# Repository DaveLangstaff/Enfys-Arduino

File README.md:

# Enfys-Arduino

Arduino code for SCPI instrument to control detector board

Dave Langstaff dpl@aber.ac.uk

Code runs on Arduino nano esp 32
Detectorboard EGSE commands
===========================
Deafult baud rate: 57600
All commands temrinated with cr-lf

Identify Command
================
*IDN?    - return identifier string. Eg "Aberystwyth University,Enfys Detector,#01,#05"

Debug Command
=============
*DBG?	 - returns debugging information on current monitors installed

Analog Input
============
AIn#?    - return data from analog inputs (ADC convertor) # is channel 0-7, channel values outside the range 0-7 will return ERR_BAD_SUFFIX -4
		 - This is a summation of OS individual readings and is returned as an unsigned long int

Set Offset DAC		 
==============
DOut# param	 - sets DAC on channel # (where channel 0=SWIR, 1=MWIR, any other # returns ERR_BAD_SUFFIX -4)
             - param is in range 0-4095, values outside this range return ERR_BAD_PARAM -5

Oversampling
============
OS param	 - set oversampling to param, where param is in the range 1-4096 values outside this range return ERR_BAD_PARAM -5
OS?			 - returns current value of oversampling

Clock speed
===========
CLK param    - sets SPI clock speed. Param should be in the range of 1,000,000 to 16,000,000 values outside this range return ERR_BAD_PARAM -5
CLK?         - return current SPI clock speed

Current and Voltage monitoring
==============================
CURR#?			return current from supply #.

					# is in the range 0-3 values outside the range 0-3 will return ERR_BAD_SUFFIX -4
					0: 3.3V supply
					
					1: Heater supply
					
					2: +12V supply
					
					3: -12V supply

VBUS#?			return bus voltage (in mV) from supply #

					# is in the range 0-3 values outside the range 0-3 will return ERR_BAD_SUFFIX -4

					0: 3.3V supply

					1: Heater supply

					2: +12V supply

					3: -12V supply
					
NAME#?			return device name from supply #

					# is in the range 0-3 values outside the range 0-3 will return ERR_BAD_SUFFIX -4

					0: 3.3V supply INA3221

					1: Heater supply INA3221

					2: +12V supply INA3221

					3: -12V supply INA260

TIME?		- gives time in usec for last read operation

BURST#?		- reads OS readings into buffer and returns whole databuffer

SCIENCE? -  reads all 8 ADC channels according to current OS and THROW parameters. Sums readings and then shifts to discard lower 4 bits
         - returns all 8 readings in a comma seperated line

DELAY xxxx 	- sets delay between SPI reads in usec

DELAY?		- returns delay between SPI reads in usec

THROW xxxx	- sets number of readings to throw away at start of each read cycle (0..1024)

THROW?		- returns number of readings to throw away at start of each read cycle (0..1024)					

HTR:ON		- enable on board heater supply

HTR:OFF		- disable on-board heater supply

POwer:ON	- Enable power to detector board

POwer:OFF	- Disable power to detector board

RTD:TEMP?	- get temperature from RTD device

  all commands will return either the requested data (? commands) 
  or an error code indicating successful or otherwise completion

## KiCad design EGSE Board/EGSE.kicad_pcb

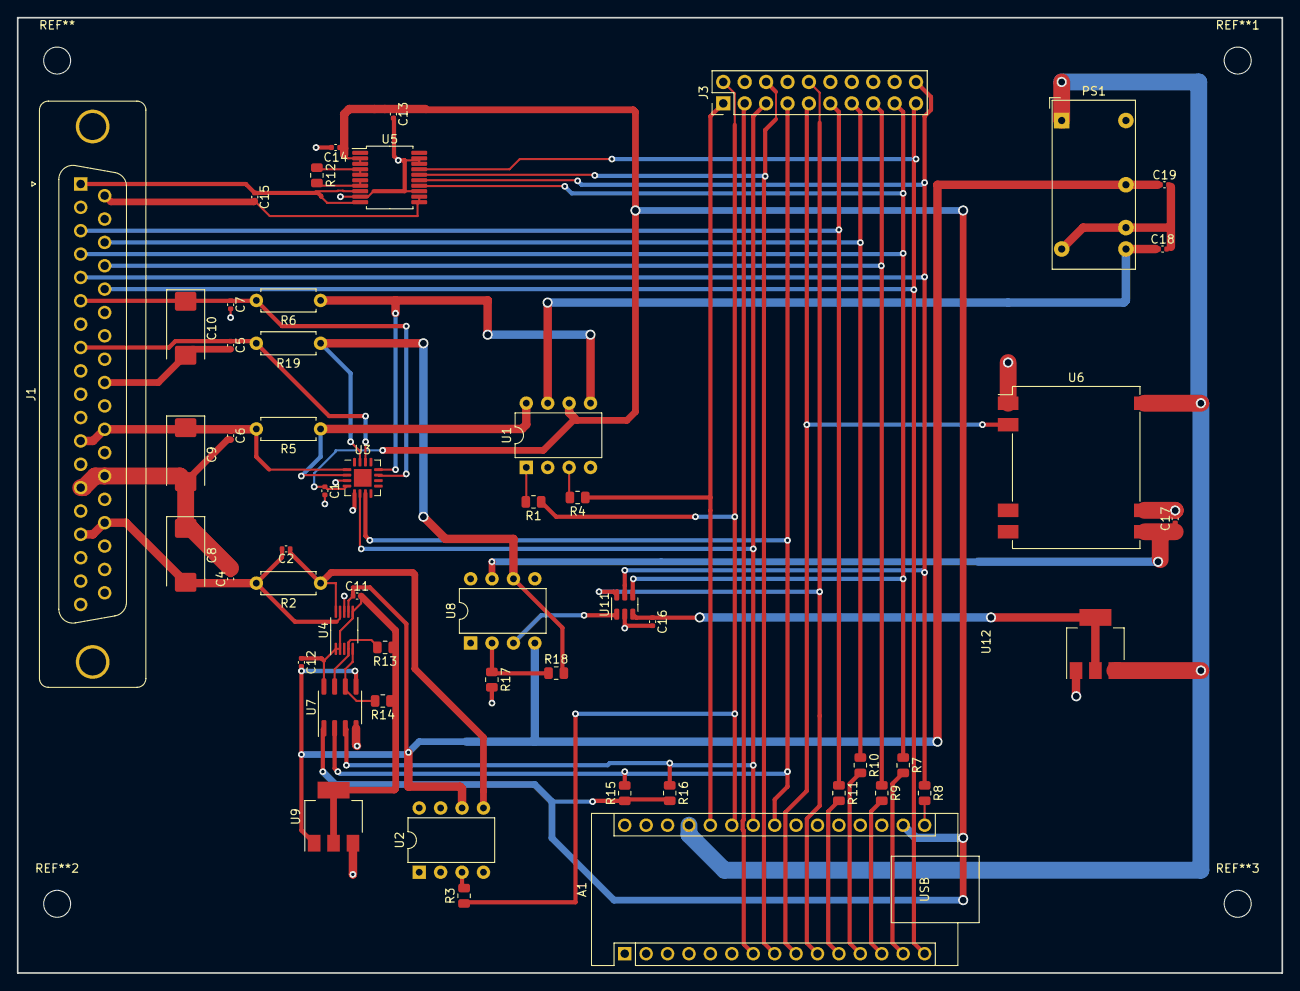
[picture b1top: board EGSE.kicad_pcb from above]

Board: 2 copper layers, 150.0 x 113.3 mm, 52 parts (0 on the bottom side), 46 nets.

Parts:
A1: Arduino_Nano_v2.x; Arduino_Nano
C1, C4, C5, C6, C7, C11, C12, C18, C19: 100nF; C_0402_1005Metric
C2: 10nF; C_0402_1005Metric
C8, C9, C10: 10uF; CP_EIA-7343-31_Kemet-D_Pad2.25x2.55mm_HandSolder
C13, C14, C15, C16, C17: 0.1u; C_0402_1005Metric
J1: DC37_Receptacle; DSUB-37_Female_Vertical_P2.77x2.84mm_MountingHoles
J3: Conn_02x10_Odd_Even; PinHeader_2x10_P2.54mm_Vertical
PS1: IR0512S; Converter_DCDC_XP_POWER-IAxxxxD_THT
R1, R3, R4: 1K; R_0805_2012Metric
R2, R5, R19: 0.1R; R_Axial_DIN0207_L6.3mm_D2.5mm_P7.62mm_Horizontal
R6: 1R; R_Axial_DIN0207_L6.3mm_D2.5mm_P7.62mm_Horizontal
R7, R8, R9, R10, R11: 33R; R_0805_2012Metric
R12: 4K; R_0805_2012Metric
R13, R14, R15, R16, R18: 3k3; R_0805_2012Metric
R17: 1k; R_0805_2012Metric
U1, U2: VOR2121A8; DIP-8_W7.62mm
U3: INA3221; Texas_RGV_S-PVQFN-N16_EP2.1x2.1mm
U4: INA238AQDGSRQ1; VSSOP-10_3x3mm_P0.5mm
U5: MAX31865xAP; SSOP-20_5.3x7.2mm_P0.65mm
U6: ISU0205S15; Converter_DCDC_XP_POWER-ISU02_SMD
U7: ISO1540; SOIC-8_3.9x4.9mm_P1.27mm
U8: OPA551P; DIP-8_W7.62mm
U9, U12: LD1117S33TR_SOT223; SOT-223-3_TabPin2
U11: DAC121S101; SOT-23-6

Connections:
+3.3V: A1.17 (3V3), C1.1, C13.1, C14.1, R15.1, R16.2, U1.6 (S2), U3.4 (VS), U5.2 (DVDD), U5.3 (VDD), U7.1 (VCC1)
+5V: A1.27 (+5V), PS1.1 (+Vin), U6.14 (+VIN), U12.3 (VI)
/-12V_UNSWITCHED: C11.1, C12.2, C19.1, PS1.4 (-Vout), U2.6 (S2), U4.7 (GND), U7.5 (GND2), U8.4 (V-), U9.1 (GND)
/BoardHeater/+12V_HTR: R18.2, R19.1, U3.15 (IN+2), U8.6
/BoardHeater/+15V: C17.1, U6.8 (+VOUT), U8.7 (V+)
/DETEC_+3v3: C7.1, C10.1, J1.6, R6.2, U3.11 (IN-1)
/DETEC_+12VA: C6.1, C9.1, J1.12, J1.30, R5.2, U3.1 (IN-3)
/DETEC_-12VA: C2.2, C4.1, C8.2, J1.16, J1.34, R2.2, U4.9 (IN-)
/DETEC_ADC_CS: J1.23, J3.15, R9.1
/DETEC_HTR: C5.1, J1.8, R19.2, U3.14 (IN-2)
/DETEC_MISO: A1.15 (D12), J1.24, J3.19, U5.17 (SDO)
/DETEC_MOSI: J1.4, J3.17, R7.1, U5.14 (SDI), U11.4 (D_IN)
/DETEC_SCK: J1.5, J3.20, R8.1, U5.15 (SCLK), U11.5 (SCLK)
/DETEC_TRP: C15.1, J1.1, U5.8 (FORCE+), U5.10 (RTDIN+)
/DETEC_TRP_RTN: C15.2, J1.20, U5.11 (RTDIN-), U5.12 (FORCE-)
/EN_3V3: A1.26 (A7), J3.1, R4.1
/EN_12V: A1.25 (A6), J3.2, R1.1, R3.1
/HTR_DAC_CS: A1.10 (D7), J3.10, U11.6 (~SYNC)
/HTR_EN: A1.9 (D6), J3.9, U6.2 (ON/~OFF)
/MWIR_DAC_CS: J1.22, J3.13, R10.1
/PowerSupplies/+12V_Unswitched: C18.1, PS1.6 (+Vout), U1.7 (S1')
/PowerSupplies/SCL2: R14.2, U4.5 (SCL), U7.6 (SCL2)
/PowerSupplies/SDA2: R13.2, U4.4 (SDA), U7.7 (SDA2)
/RTD_MON_CS: A1.8 (D5), J3.6, U5.16 (~CS)
/SCL: A1.24 (A5), J3.5, R16.1, U3.6 (SCL), U7.3 (SCL1)
/SDA: A1.23 (A4), J3.7, R15.2, U3.7 (SDA), U7.2 (SDA1)
/SWIR_DAC_CS: J1.3, J3.11, R11.1
/TRIG: A1.7 (D4), J3.3
GND: A1.4 (GND), A1.29 (GND), C1.2, C4.2, C5.2, C6.2, C7.2, C8.1, C9.2, C10.2, C13.2, C14.2, C16.2, C17.2, C18.2, C19.2, J1.14, J1.25, J1.28, J1.32, J3.4, J3.8, J3.14, J3.18, PS1.2 (-Vin), PS1.5 (0V), R17.2, U1.2, U1.4, U2.4, U3.3 (GND), U3.5 (A0), U4.8 (VBUS), U5.9 (FORCE2), U5.13 (GND), U5.18 (DGND), U5.19 (GND), U6.1 (-VIN), U6.9 (-VOUT), U7.4 (GND1), U9.3 (VI), U11.2 (GND), U12.1 (GND)
unnamed: A1.11 (D8), R11.2
unnamed: A1.12 (D9), R10.2
unnamed: A1.13 (D10), R9.2
unnamed: A1.14 (D11), R7.2
unnamed: A1.16 (D13), R8.2
unnamed: R1.2, U1.1
unnamed: R3.2, U2.3
unnamed: R4.2, U1.3
unnamed: R5.1, U1.8 (S1), U3.2 (IN+3)
unnamed: R6.1, U1.5 (S2'), U3.12 (IN+1)
unnamed: C2.1, R2.1, U2.5 (S2'), U4.10 (IN+)
unnamed: C11.2, C12.1, R13.1, R14.1, U4.1 (A1), U4.2 (A0), U4.6 (VS), U7.8 (VCC2), U9.2 (VO)
unnamed: R12.1, U5.4 (BIAS), U5.5 (REFIN+)
unnamed: R12.2, U5.6 (REFIN-), U5.7 (ISENSOR)
unnamed: R17.1, R18.1, U8.2 (-)
unnamed: U8.3 (+), U11.1 (Va)
unnamed: C16.1, U11.3 (+V_A), U12.2 (VO)

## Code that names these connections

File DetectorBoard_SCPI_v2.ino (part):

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#include <Adafruit_MAX31865.h>


#define DETEC_SCK   13//sck
#define DETEC_MISO  12//CIPO
#define DETEC_MOSI  11//COPI
#define DETEC_ADC_CS  10//cs
#define MWIR_DAC_CS  9 //cs
#define SWIR_DAC_CS  8 //cs
#define HTR_DAC_CS   7 // DAC for board heater current control
#define HTR_EN       6 // Enable board heater supply
#define RTD_MON_CS   5 // Enable for board temperature monitor
#define TRIG         4 // Trigger for scope
#define TRIG2        3 // Trigger for light source

// IN238 and INA3221 current monitors are both on the I2C bus
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INA_Class      INA;                      ///< INA class instantiation to use EEPROM


#define EN_3V3      A7 // enable pin for 3v3 power
#define EN_12V      A6 // enable pin for 12v power

#define ClockSpeed 1000000   //1MHz SPI clock (default)
#define minClk 100000     // 100KHz minimum clock
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
  // setup SPI bus
  ClkSpeed = ClockSpeed;
  pinMode(DETEC_MOSI, OUTPUT); 
  pinMode(DETEC_SCK,OUTPUT);
  pinMode(SWIR_DAC_CS,OUTPUT); digitalWrite(SWIR_DAC_CS,HIGH);
  pinMode(MWIR_DAC_CS,OUTPUT); digitalWrite(MWIR_DAC_CS,HIGH);
  pinMode(TRIG,OUTPUT);  digitalWrite(TRIG,HIGH);
  pinMode(TRIG2,OUTPUT);  digitalWrite(TRIG2,LOW);
  pinMode(DETEC_ADC_CS,OUTPUT);  digitalWrite(DETEC_ADC_CS,HIGH);
  pinMode(DETEC_MISO, INPUT);
  //Serial.println("Pins allocated");

  SPI.begin();
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
  
  // setup pins for power rail control
  pinMode(EN_3V3, OUTPUT); digitalWrite(EN_3V3, LOW);
  pinMode(EN_12V, OUTPUT); digitalWrite(EN_12V, LOW);
  // Blue LED used as power indicator. Start turned OFF, turns on with POWER:ON command
  pinMode(LED_BLUE, OUTPUT); digitalWrite(LED_BLUE, HIGH); // N LED drive is inverted

  // pins for heater control
  pinMode(HTR_EN, OUTPUT); digitalWrite(HTR_EN, HIGH);    // HTR enable pin, active LOW
  pinMode(HTR_DAC_CS, OUTPUT); digitalWrite(HTR_DAC_CS, HIGH);  // HTR DAC enable, active low
  // set heater DAC to 0
  SPI.beginTransaction(SPISettings(ClkSpeed, MSBFIRST, SPI_MODE1));
  digitalWrite(HTR_DAC_CS, LOW);           // select heater DAC
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
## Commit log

2024-01-23 Add files via upload
    Initial version for version control
2024-01-29 BURST,#? DELAY and TIME? commands added
    Commands added for
    BURST#? - burst mode output
    DELAY - sets delay between reads
    TIME? - gives total time for read cycle
2024-01-30 Made OS sample size
    Changed OS and OS? to work with OSvalue rather than OSLevel
    Allows choice of any nuber of samples in range 1..1024
2024-01-30 Add dummy read
    Added a dummy read at start of ReadADCtoBuffer to allow for the fact that first reading on new channel is wrong.
2024-02-01 OS upgrade
    Defined Oversampling using MaxDataSize definition so facilitte changing it.
    Added THROW and THROW? to set throwAway defining how many samples to throw away before starting to fill the buffer
2024-02-01 With error codes
    All commands now return error codes
    ERR_NO_ERROR 0
    ERR_BAD_COMMAND -1
    ERR_TIMEOUT -2
    ERR_BUFF_OVERFLOW -3
    ERR_BAD_SUFFIX -4
2024-02-07 Fixed off-by-one errors with THROW and OS
2024-02-07 Fixed off-by-one in BURST mode command
2024-02-10 Added EGSE Board
2024-02-10 Added EGSE Board
    Added Kicad files for EGCE board based on Arduino Nano
2024-02-11 Major update
    Changed name to EGSE
    Udated design to include current pmonitors
    Imported symbols and footprints for SSR, DCDC convertor & IN238 current monitors
2024-02-12 Split Sheets
    Added sheet to cover Power supplies and monitoring
    Modified design to have monitor for -12VA supply running of -12V line with isolated I2C but
2024-02-14 EGSE board updates
2024-02-14 Change to heater power
2024-02-16 Friday updates. PCB first draft
2024-02-21 Regular update
    Created Gerber files for production
    Changed names in arduino code to reflect signal names used by MSSL and on EGSE board
2024-02-21 Update Arduino code
    Updated Arduino code to reflect names used on EGSE board
    Added libraries for INA devices (current monitors) and MAX31865 (RTD reading)
2024-02-26 PCB Second draft
    Final PCB and Gerber files for production
2024-03-08 SCPI Parser fix
    Changed SCPI_HASH_TYPE to avoid hash conflicts
    Moved SCPI defines to above the line including vrekrer_scpi_parser.h
    Added commands to interface with INA3xxx current monitor and MAX31865 RTD controller
    Added *DBG command to print debug information from parser
2024-06-25 Update DetectorBoard_SCPI_v2.ino
    Added CLK and CLK? to set and query SPI clock
2024-10-09 Major update
    Moved ID & version string to top of file for ease of use.
    Increased MAX_TOKENS in SCPI parser
    Defined TRIG2 to work with BNC connector added to EGSE board
    Defined 0R15 ohm shunt resistor for INA devices
    Increased oversample and throwaway maximums to 4096
    Added ClkSpeed variable along with SetClkSpeed() and GetCLkspeed functions as well as CLK and CLK? commands for SCPI parser.
2024-10-09 Major update
    Moved ID & version string to top of file for ease of use.
    Increased MAX_TOKENS in SCPI parser
    Defined TRIG2 to work with BNC connector added to EGSE board
    Defined 0R15 ohm shunt resistor for INA devices
    Increased oversample and throwaway maximums to 4096
    Added ClkSpeed variable along with SetClkSpeed() and GetCLkspeed functions as well as CLK and CLK? commands for SCPI parser.
2024-10-15 Updates
    Updated description of commands, both in readme.txt and also at head of code.
    Used symbolic definition for maxHeaterDAC
    reduced serialSpeed to 57600
2024-11-15 Modify elapsed timing
    Moved assignment to Starttime in ReadADCtoBuffer() so as to include throwaway reads.
2024-11-15 SCIENCE Added
    Added SCIENCE? command to command set.
    This will read all 8 ADC channels according to current THROW and OS parameters. Each channel is summed and the result bit shifted to drop the 4 LSBs before returning data from all 8 channels as a com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
2024-11-21 Implement SCIENCE packet
    Implemented Science packet introduced in last change.
    Reserve array of int to hold 8 science words
    Updated version number in ID string
    Added RegisterCommand for getScience function
    Implemented getScienceFunction
2025-08-04 Changed version number to 2.3 Removed routines and commands referring to HTR_DAC Ensured all SPI bus lines are held low before 3v3 and 12v power applied to board SPI_CS bus lines set high after 3v3 a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
2025-08-04 Enabled DOUT#? to read back value set on SWIR and MWIR DACs Arranged SWIR and MWIR DACs to be set to 100 at initial power on
2025-08-04 Update Readme.txt
    Removed reference to HTR:DAC commands
    Added command DOUT#? to read value previously set on one of the DAC channels
2025-08-05 V2.5 Changed to using MODE3 for reading out ADC
    V2.6
    Set default and minimum value of throwAway to 1 (ADC datasheet - first read is of random channel
    Updated setThrowAway to use minimum value of 1 for Throwaway
    Removed extra toggling of DETEC_ADC_CS to read all of one ADC channel continuously
2025-09-03 Added facility to disable access to any functions that interact with the SPI bus while the power is not applied. This is to ensure that all SPI lines are low when power is not applied to the detector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
2025-11-11 Removed extraneous version of code from repo
2025-11-21 Enhance README with Detectorboard commands
    Added detailed command descriptions for Detectorboard EGSE.
2025-11-21 Correct typos in README commands section
    Fix typos and formatting issues in README.
2025-11-21 Update README with current and voltage monitoring info
    Added details for current and voltage monitoring commands.
2025-11-21 Fix typos and improve formatting in README
    Corrected typos and formatting in command descriptions.
2025-11-21 Clarify VBUS#? return value description
    Updated VBUS#? description for clarity.
2025-11-21 Revise README for VBUS and NAME command descriptions
    Updated documentation for VBUS and NAME commands with additional details.
2025-11-21 Update README with power and temperature commands
    Added commands for power control and temperature retrieval.
